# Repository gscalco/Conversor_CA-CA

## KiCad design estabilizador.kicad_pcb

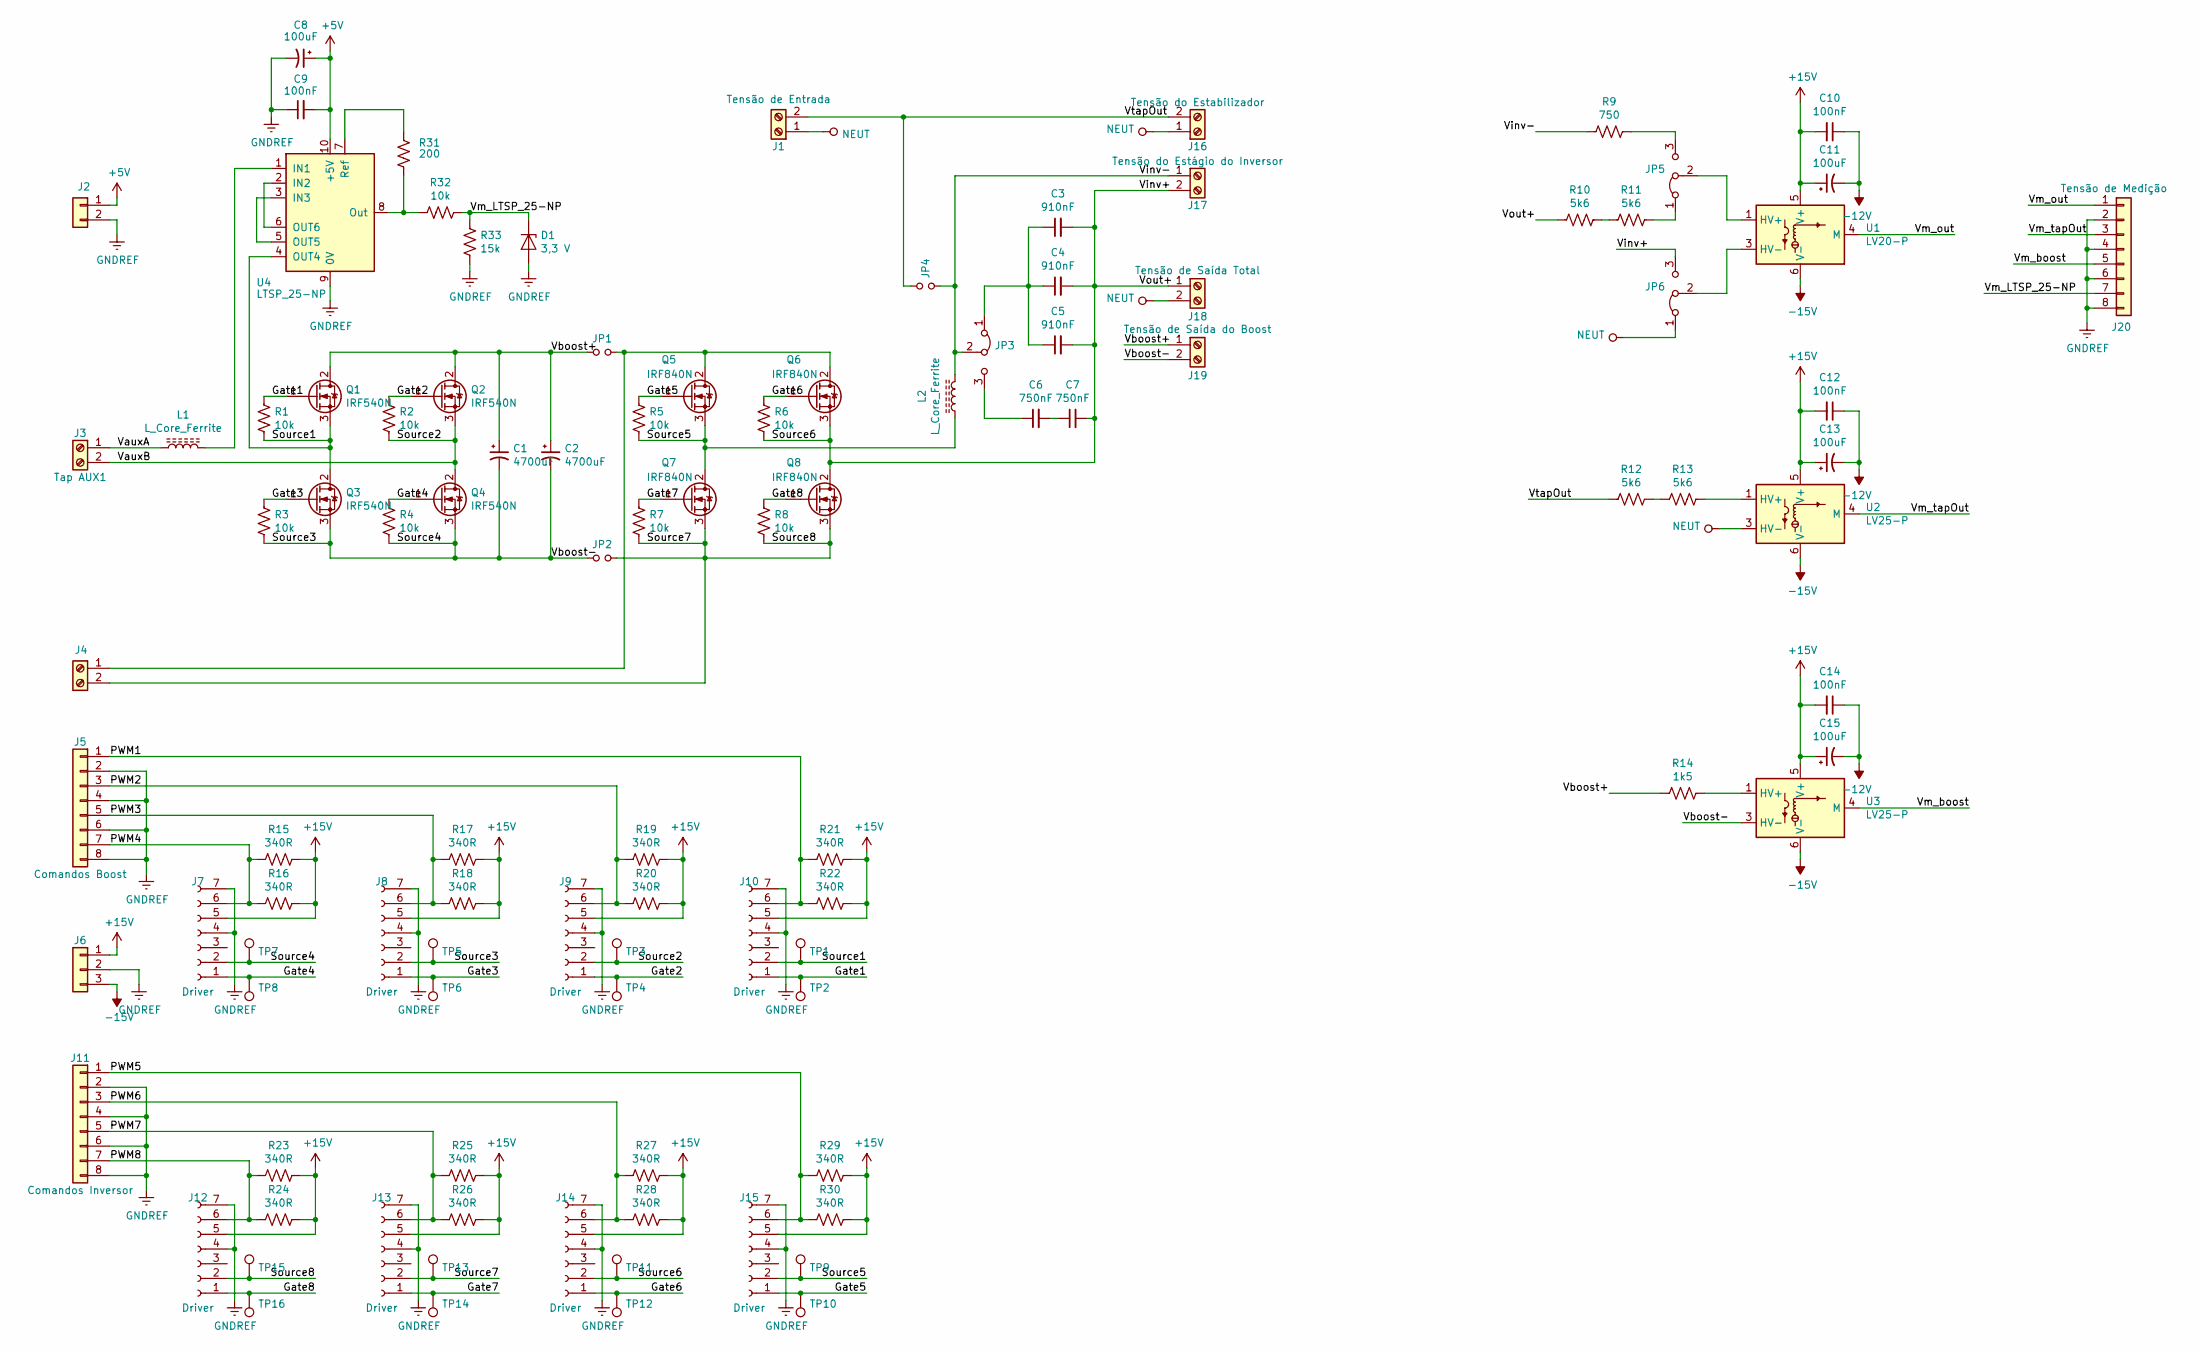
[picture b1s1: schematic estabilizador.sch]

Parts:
C1, C2: 4700uF; CP_Radial_D18.0mm_P7.50mm
C3, C4, C5: 910nF; C_Rect_L29.0mm_W7.6mm_P27.50mm_MKT
C6, C7: 750nF; C_Rect_L26.5mm_W7.0mm_P22.50mm_MKS4
C8, C11, C13, C15: 100uF; CP_Elec_8x10
C9, C10, C12, C14: 100nF; C_0805_2012Metric_Pad1.15x1.40mm_HandSolder
D1: 3,3 V; D_DO-35_SOD27_P7.62mm_Horizontal
J1: Tensão de Entrada; PhoenixContact_MSTBVA_2,5_2-G-5,08_1x02_P5.08mm_Vertical
J2: Fonte Aux2; PinHeader_1x02_P2.54mm_Vertical
J3: Tap AUX1; PhoenixContact_MSTBVA_2,5_2-G-5,08_1x02_P5.08mm_Vertical
J4: Screw_Terminal_01x02; PhoenixContact_MSTBVA_2,5_2-G-5,08_1x02_P5.08mm_Vertical
J5: Comandos Boost; PinHeader_1x08_P2.54mm_Vertical
J6: Fonte Aux; PinHeader_1x03_P2.54mm_Vertical
J7, J8, J9, J10, J12, J13, J14, J15: Driver; PinHeader_1x07_P2.54mm_Vertical
J11: Comandos Inversor; PinHeader_1x08_P2.54mm_Vertical
J16: Tensão do Estabilizador; PhoenixContact_MSTBVA_2,5_2-G-5,08_1x02_P5.08mm_Vertical
J17: Tensão do Estágio do Inversor; PhoenixContact_MSTBVA_2,5_2-G-5,08_1x02_P5.08mm_Vertical
J18: Tensão de Saída Total; PhoenixContact_MSTBVA_2,5_2-G-5,08_1x02_P5.08mm_Vertical
J19: Tensão de Saída do Boost; PhoenixContact_MSTBVA_2,5_2-G-5,08_1x02_P5.08mm_Vertical
J20: Tensão de Medição; PinHeader_1x08_P2.54mm_Vertical
JP1, JP2, JP4: Jumper_NO_Small; PinHeader_1x02_P2.54mm_Vertical
JP3, JP5, JP6: Jumper_3_Bridged12; PinHeader_1x03_P2.54mm_Vertical
L1: L_Core_Ferrite; NEE_30-14
L2: L_Core_Ferrite; NEE_42-20
Q1, Q2, Q3, Q4: IRF540N; TO-220-3 Heatsink
Q5, Q6, Q7, Q8: IRF840N; TO-220-3 Heatsink
R1, R2, R3, R4, R5, R6, R7, R8: 10k; R_0805_2012Metric_Pad1.15x1.40mm_HandSolder
R9: 750; R_Axial_DIN0207_L6.3mm_D2.5mm_P10.16mm_Horizontal
R10, R11, R12, R13: 5k6; R_Axial_DIN0411_L9.9mm_D3.6mm_P15.24mm_Horizontal
R14: 1k5; R_Axial_DIN0309_L9.0mm_D3.2mm_P12.70mm_Horizontal
R15, R16, R17, R18, R19, R20, R21, R22, R23, R24, R25, R26, R27, R28, R29, R30: 340R; R_1206_3216Metric_Pad1.42x1.75mm_HandSolder
R31: 200; R_1206_3216Metric_Pad1.42x1.75mm_HandSolder
R32: 10k; R_1206_3216Metric_Pad1.42x1.75mm_HandSolder
R33: 15k; R_1206_3216Metric_Pad1.42x1.75mm_HandSolder
TP1, TP2, TP3, TP4, TP5, TP6, TP7, TP8, TP9, TP10, TP11, TP12, TP13, TP14, TP15, TP16: TestPoint; PinHeader_1x01_P2.54mm_Vertical
U1: LV20-P; LEM_LV25-P
U2, U3: LV25-P; LEM_LV25-P
U4: LTSP_25-NP; LEM_LTSR-NP

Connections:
+5V: C8.1, C9.2, J2.1, U4.10 (+5V)
+15V: C10.2, C11.1, C12.2, C13.1, C14.2, C15.1, J6.1, J7.5, J8.5, J9.5, J10.5, J12.5, J13.5, J14.5, J15.5, R15.1, R16.1, R17.1, R18.1, R19.1, R20.1, R21.1, R22.1, R23.1, R24.1, R25.1, R26.1, R27.1, R28.1, R29.1, R30.1, U1.5 (V+), U2.5 (V+), U3.5 (V+)
/Gate1: J10.1, Q1.1 (G), R1.1, TP2.1
/Gate2: J9.1, Q2.1 (G), R2.1, TP4.1
/Gate3: J8.1, Q3.1 (G), R3.1, TP6.1
/Gate4: J7.1, Q4.1 (G), R4.1, TP8.1
/Gate5: J15.1, Q5.1 (G), R5.1, TP10.1
/Gate6: J14.1, Q6.1 (G), R6.1, TP12.1
/Gate7: J13.1, Q7.1 (G), R7.1, TP14.1
/Gate8: J12.1, Q8.1 (G), R8.1, TP16.1
/PWM1: J5.1, J10.6, R21.2, R22.2
/PWM2: J5.3, J9.6, R19.2, R20.2
/PWM3: J5.5, J8.6, R17.2, R18.2
/PWM4: J5.7, J7.6, R15.2, R16.2
/PWM5: J11.1, J15.6, R29.2, R30.2
/PWM6: J11.3, J14.6, R27.2, R28.2
/PWM7: J11.5, J13.6, R25.2, R26.2
/PWM8: J11.7, J12.6, R23.2, R24.2
/Source1: J10.2, Q1.3 (S), Q3.2 (D), R1.2, TP1.1, U4.4 (OUT4)
/Source2: J3.2, J9.2, Q2.3 (S), Q4.2 (D), R2.2, TP3.1
/Source3: C1.2, C2.2, J7.2, J8.2, J19.2, JP2.2, Q3.3 (S), Q4.3 (S), R3.2, R4.2, TP5.1, TP7.1, U3.3 (HV-)
/Source5: J15.2, L2.1, Q5.3 (S), Q7.2 (D), R5.2, TP9.1
/Source6: C3.2, C4.2, C5.2, C7.2, J14.2, J17.2, J18.1, JP6.3 (B), Q6.3 (S), Q8.2 (D), R6.2, R10.2, TP11.1
/Source7: J4.2, J12.2, J13.2, JP2.1, Q7.3 (S), Q8.3 (S), R7.2, R8.2, TP13.1, TP15.1
/VauxA: J3.1, L1.2
/Vboost+: C1.1, C2.1, J19.1, JP1.2, Q1.2 (D), Q2.2 (D), R14.2
/Vinv-: J17.1, JP3.2 (C), JP4.2, L2.2, R9.2
/Vm_LTSP_25-NP: D1.1 (K), J20.7, R32.1, R33.2
/Vm_boost: J20.5, U3.4 (M)
/Vm_out: J20.1, U1.4 (M)
/Vm_tapOut: J20.3, U2.4 (M)
/VtapOut: J1.2, J16.2, JP4.1, R12.2; also elsewhere on the board
GNDREF: C8.2, C9.1, D1.2 (A), J2.2, J5.2, J5.4, J5.6, J5.8, J6.2, J7.4, J7.7, J8.4, J8.7, J9.4, J9.7, J10.4, J10.7, J11.2, J11.4, J11.6, J11.8, J12.4, J12.7, J13.4, J13.7, J14.4, J14.7, J15.4, J15.7, J20.2, J20.4, J20.6, J20.8, R33.1, U4.9 (0V)
NEUT: J1.1, J16.1, J18.2, JP6.1 (A), U2.3 (HV-)
unnamed: C3.1, C4.1, C5.1, JP3.1 (A)
unnamed: C6.1, JP3.3 (B)
unnamed: C6.2, C7.1
unnamed: J4.1, JP1.1, Q5.2 (D), Q6.2 (D)
unnamed: JP5.1 (A), R11.1
unnamed: JP5.2 (C), U1.1 (HV+)
unnamed: JP5.3 (B), R9.1
unnamed: JP6.2 (C), U1.3 (HV-)
unnamed: L1.1, U4.1 (IN1)
unnamed: R10.1, R11.2
unnamed: R12.1, R13.2
unnamed: R13.1, U2.1 (HV+)
unnamed 54: R14.1, U3.1 (HV+); also elsewhere on the board
unnamed: R31.1, R32.2, U4.8 (Out)
unnamed: R31.2, U4.7 (Ref)
unnamed: U4.2 (IN2), U4.6 (OUT6)
unnamed: U4.3 (IN3), U4.5 (OUT5)

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
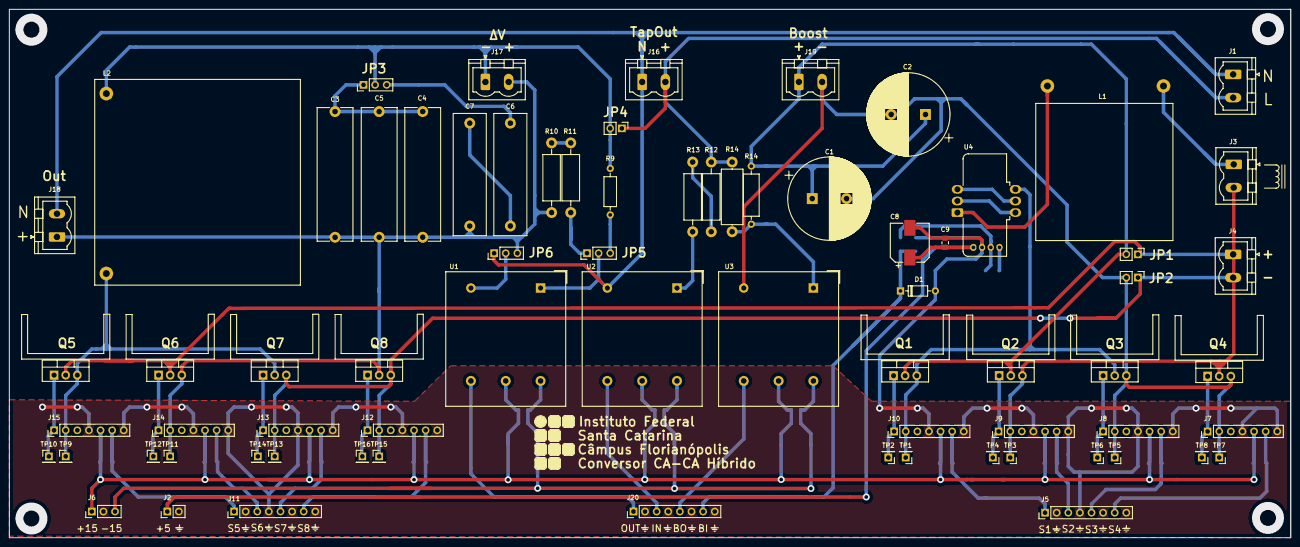
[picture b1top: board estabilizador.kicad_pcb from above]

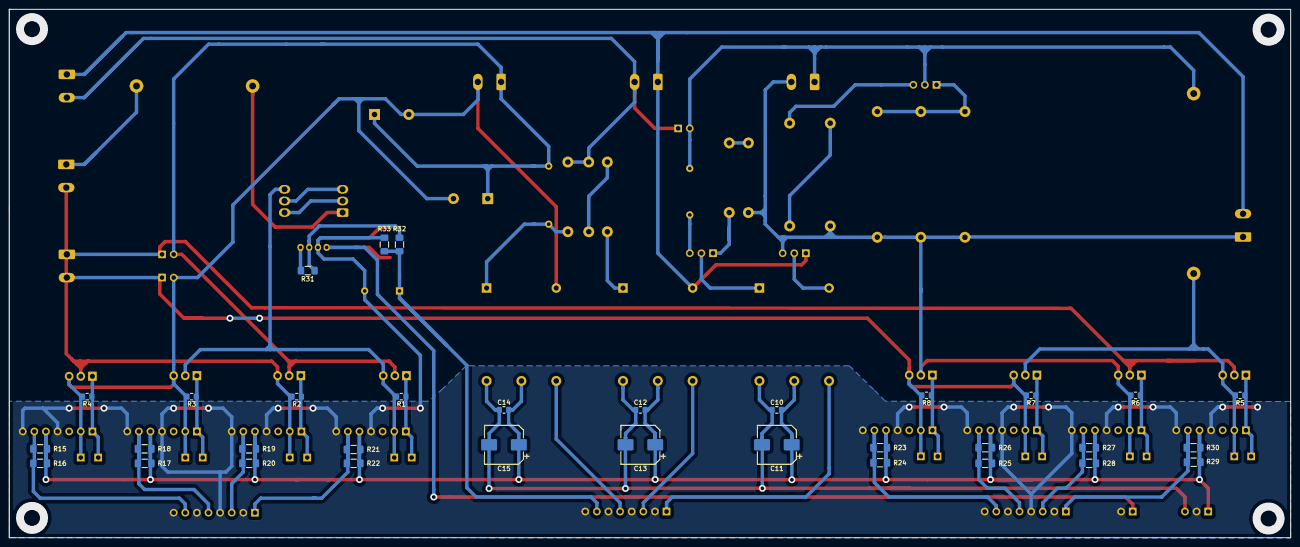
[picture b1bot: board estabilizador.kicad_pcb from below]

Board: 2 copper layers, 280.3 x 115.6 mm, 106 parts (33 on the bottom side), 52 nets.

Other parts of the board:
R14#2: 10K; R_Axial_DIN0414_L11.9mm_D4.5mm_P15.24mm_Horizontal

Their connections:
/VtapOut: R14#2.2; also elsewhere on the board
unnamed 54: R14#2.1; also elsewhere on the board

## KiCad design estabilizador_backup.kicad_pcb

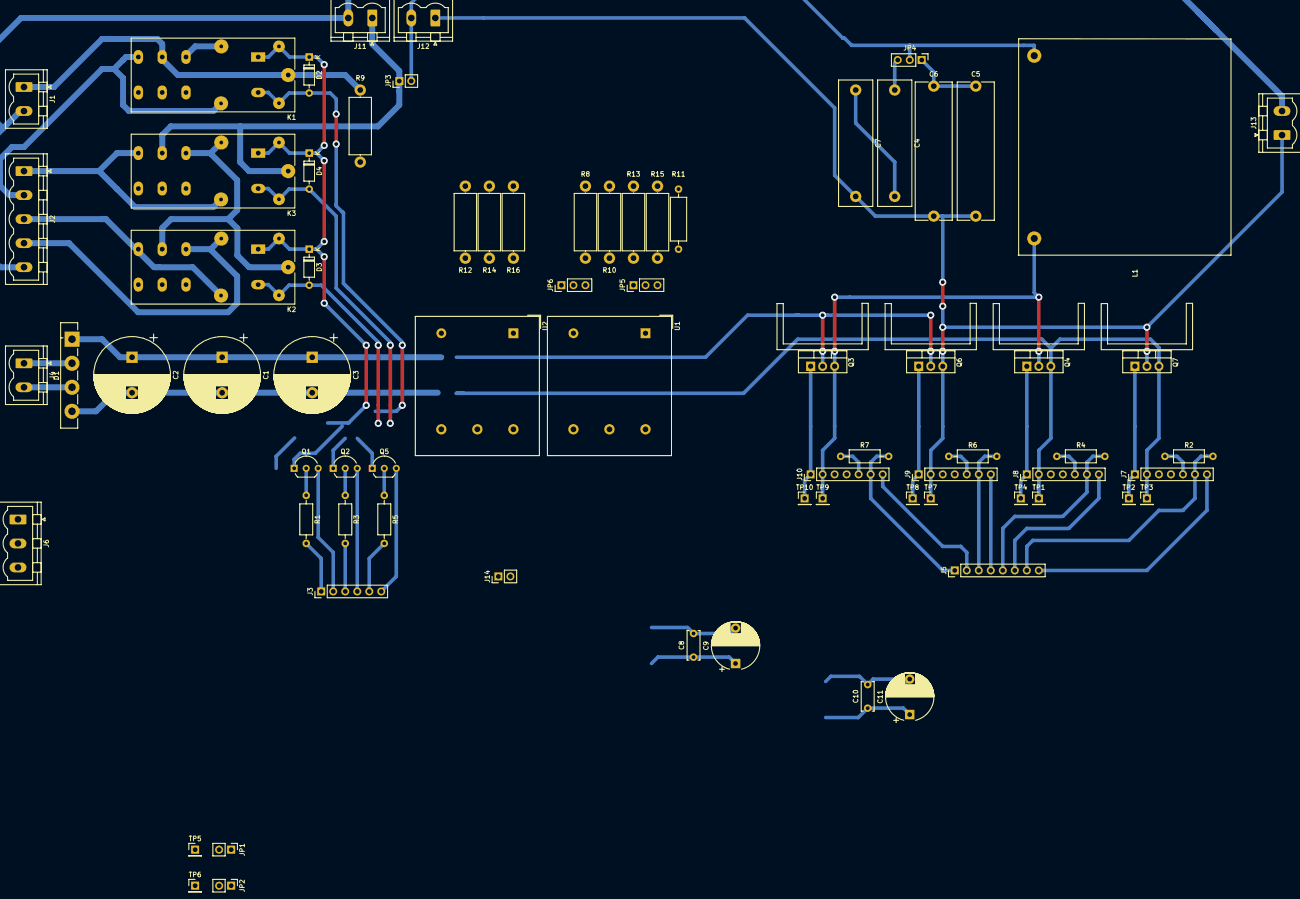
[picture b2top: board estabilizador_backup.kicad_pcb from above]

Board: 2 copper layers, 74 parts (0 on the bottom side), 53 nets.

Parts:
C1, C2, C3: 1000uF; CP_Radial_D16.0mm_P7.50mm
C4, C7: 390nF; C_Rect_L26.5mm_W7.0mm_P22.50mm_MKS4
C5, C6: 690nF; C_Rect_L29.0mm_W7.6mm_P27.50mm_MKT
C8, C10: 100nF; C_Disc_D6.0mm_W2.5mm_P5.00mm
C9, C11: 100uF; CP_Radial_D10.0mm_P7.50mm
D1: GBU8J; Diode_Bridge_Vishay_GBU
D2, D3, D4: 1N4148; D_DO-35_SOD27_P7.62mm_Horizontal
J1: Tensão de Entrada; PhoenixContact_MSTBVA_2,5_2-G-5,08_1x02_P5.08mm_Vertical
J2: Autotransformador; PhoenixContact_MSTBVA_2,5_5-G-5,08_1x05_P5.08mm_Vertical
J3: Comandos Reles; PinHeader_1x06_P2.54mm_Vertical
J4: Tap auxiliar; PhoenixContact_MSTBVA_2,5_2-G-5,08_1x02_P5.08mm_Vertical
J5: Comandos PWMs; PinHeader_1x08_P2.54mm_Vertical
J6: Fonte Aux; PhoenixContact_MSTBVA_2,5_3-G-5,08_1x03_P5.08mm_Vertical
J7, J8, J9, J10: Driver; PinHeader_1x07_P2.54mm_Vertical
J11: Tensão do Estágio de Reles; PhoenixContact_MSTBVA_2,5_2-G-5,08_1x02_P5.08mm_Vertical
J12: Tensão do Estágio do Inversor; PhoenixContact_MSTBVA_2,5_2-G-5,08_1x02_P5.08mm_Vertical
J13: Tensão de Saída Total; PhoenixContact_MSTBVA_2,5_2-G-5,08_1x02_P5.08mm_Vertical
J14: Tensão de Medição; PinHeader_1x02_P2.54mm_Vertical
JP1, JP2, JP3: Jumper_NO_Small; PinHeader_1x02_P2.54mm_Vertical
JP4, JP5, JP6: Jumper_3_Bridged12; PinHeader_1x03_P2.54mm_Vertical
K1, K2, K3: RT42xxxx; Relay_DPDT_model_B
L1: L_Core_Ferrite; Inductor_EE4220
Q1, Q2, Q5: BC517; TO-92_Inline_Wide
Q3, Q4, Q6, Q7: IRF840N; TO-220-3 Heatsink
R1, R3, R5: 100K; R_Axial_DIN0207_L6.3mm_D2.5mm_P10.16mm_Horizontal
R2, R4, R6, R7: 340R; R_Axial_DIN0207_L6.3mm_D2.5mm_P10.16mm_Horizontal
R8, R9, R10, R12: 1K; R_Axial_DIN0414_L11.9mm_D4.5mm_P15.24mm_Horizontal
R11: 3K3; R_Axial_DIN0309_L9.0mm_D3.2mm_P12.70mm_Horizontal
R13, R14, R15, R16: 2K2; R_Axial_DIN0414_L11.9mm_D4.5mm_P15.24mm_Horizontal
TP1, TP2, TP3, TP4, TP5, TP6, TP7, TP8, TP9, TP10: TestPoint; PinHeader_1x01_P2.54mm_Vertical
U1, U2: LV25-P; LEM_LV25-P

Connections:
+12V: C8.2, C9.1, C10.2, C11.1, D2.1, D3.1, D4.1, J6.1, J7.5, J8.5, J9.5, J10.5, K1.A2, K2.A2, K3.A2, R2.1, R4.1, R6.1, R7.1, U1.5, U2.5
-12V: C8.1, C9.2, C10.1, C11.2, J6.3, U1.6, U2.6
/Gate1: J10.1, Q3.1, TP10.1
/Gate2: J9.1, Q6.1, TP8.1
/Gate3: J8.1, Q4.1, TP4.1
/Gate4: J7.1, Q7.1, TP2.1
/HI_in_inv: JP1.1, Q3.2, Q6.2
/LO_in_inv: J7.2, J8.2, JP2.1, Q4.3, Q7.3, TP1.1, TP3.1
/PWM1: J5.1, J10.6, R7.2
/PWM2: J5.3, J9.6, R6.2
/PWM3: J5.5, J8.6, R4.2
/PWM4: J5.7, J7.6, R2.2
/RL1: J3.1, R1.2
/RL2: J3.3, R3.2
/RL3: J3.5, R5.2
/Source1: J10.2, L1.1, Q3.3, Q4.2, TP9.1
/Source2: C5.2, C6.2, C7.2, J9.2, J12.1, J13.1, JP6.3, Q6.3, Q7.2, R8.2, TP7.1
/VauxA: D1.2, J4.1
/VauxB: D1.3, J4.2
/Vinv+: J12.2, JP3.2, JP4.2, L1.2, R11.2
/Vm_in: J14.1, U2.4
/Vm_out: J14.2, U1.4
/Vtap1: J2.1, K3.24
/Vtap2: J2.3, K2.24
/Vtap3: J2.4, K2.22
/VtapIn: J2.2, K1.24
/VtapOut: J11.1, JP3.1, K3.21
GNDREF: J3.2, J3.4, J3.6, J5.2, J5.4, J5.6, J5.8, J6.2, J7.4, J7.7, J8.4, J8.7, J9.4, J9.7, J10.4, J10.7, Q1.3, Q2.3, Q5.3
LINE: J1.1, K1.21, R9.2
NEUT: J1.2, J2.5, J11.2, J13.2, JP6.1, U2.3
unnamed: C1.1, C2.1, C3.1, D1.1, JP1.2, TP5.1
unnamed: C1.2, C2.2, C3.2, D1.4, JP2.2, TP6.1
unnamed: C4.1, JP4.3
unnamed: C4.2, C7.1
unnamed: C5.1, C6.1, JP4.1
unnamed: D2.2, K1.A1, Q1.1
unnamed: D3.2, K2.A1, Q2.1
unnamed: D4.2, K3.A1, Q5.1
unnamed: JP5.1, R15.1
unnamed: JP5.2, U1.1
unnamed: JP5.3, R11.1
unnamed: JP6.2, U1.3
unnamed: K2.21, K3.22
unnamed: Q1.2, R1.1
unnamed: Q2.2, R3.1
unnamed: Q5.2, R5.1
unnamed: R10.1, R13.2
unnamed: R8.1, R10.2
unnamed: R12.1, R14.2
unnamed: R9.1, R12.2
unnamed: R13.1, R15.2
unnamed: R14.1, R16.2
unnamed: R16.1, U2.1

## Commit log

2020-02-28 Original
2020-02-29 Modificação do esquemático
2020-02-29 Modificação da PCB
2020-03-02 Modificação do esquemático e PCB
2020-03-03 Alteração das labels/Finalização PCB
2020-03-10 Modificação driver IGBT/LTSP25_NP
2020-03-10 Adição dos Testpoints
2020-03-19 Modificação drivers e chaves
